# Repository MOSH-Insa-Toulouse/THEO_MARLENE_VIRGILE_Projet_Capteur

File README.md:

# THEO_MARLENE_VIRGILE_Projet_Capteur
Ce projet s'inscrit dans l'UF **"Du capteur au banc de Test"** en 4ème année Génie Physique, à l'INSA de Toulouse. 
***
Ce dernier a pour but l'élaboration d'un **capteur de déformation** à bas coût à base de graphite, dont le fonctionnement est basé sur le principe de déplacement des électrons entre les nanoparticules par effet tunnel. 
La contrainte mécanique appliquée modifiant la distance entre les particules, la conductivité électrique de la couche de graphite subit elle aussi une modification. La déformation du capteur créé grâce à un dépôt au crayon à papier engendre donc une variation de résistance alors mesurable.
*** 
Dans ce dossier sont présentées les différentes étapes que nous avons suivies : du design de notre shield, à notre code Arduino en passant par la réalisation d'une application pour téléphone et d'un banc de mesure réalisé en impression 3D. 

## Sommaire 

* [1. Description du projet et détail des livrables](#PremiereSection) 
* [2. Arduino](#DeuxiemeSection)
  * [2.1. Librairies utilisées](#DeuxiemeSection1)
  * [2.2. Code Arduino](#DeuxiemeSection2)
* [3. KICAD](#TroisiemeSection)  
  * [3.1 Symboles et empreintes](#TroisiemeSection1)
  * [3.2 Schématique](#TroisiemeSection2)
  * [3.3 Placement des composants](#TroisiemeSection3)
  * [3.4 Visualisation 3D](#TroisiemeSection4)
* [4. Fabrication du shield](#QuatriemeSection)
  * [4.1 Réalisation du PCB](#QuatriemeSection1)
  * [4.2 Perçage et soudure](#QuatriemeSection2)
* [5. Application Android](#CinquiemeSection) 
* [6. Tests](#SixiemeSection)
  * [6.1. Banc de test](#SixiemeSection1)
  * [6.2. Résultats obtenus](#SixiemeSection2)
  * [6.3. Analyse des résultats et discussion](#SixiemeSection3)
* [7. Datasheet](#SeptiemeSection)

## 1. Description du projet et détail des livrables

Liste des livrables :

- [x] Un code Arduino permettant une mesure de résistance et un contrôle des fonctionnalités Bluetooth, OLED... 
- [x] Un shield PCB
- [x] Une application android APK 
- [x] Un protocole du banc de test
- [x] Une datasheet des capteurs de déformation

Dans un premier temps, nous avons réalisé un **code Arduino** fonctionnel permettant de contrôler un amplificateur transimpédance, un encodeur rotatoire, un écran OLED ainsi qu'un module Bluetooth. Nous l'avons ensuite testé en effectuant nos premiers branchements.
Ensuite, nous avons réalisé le design de notre **shield** à l'aide du logiciel *KICAD*, nous l'avons fabriqué, puis nous avons assemblé nos composants dessus.   
A la suite de cela, nous avons utilisé le logiciel *MIT App Inventor* afin de développer une **application téléphone APK**, capable de communiquer et recevoir des données à distance à l'aide du module Bluetooth (notamment de récupérer la résistance ressentie par le capteur et de l'afficher sur un graphique).    
Nous avons également designé puis réalisé, un **banc de mesure** en impression 3D, qui, à l'aide d'un servomoteur nous permet de caractériser la réponse en déformation de nos futurs capteurs.   
Finalement, nous sommes passés à la phase de tests et avons créé nos capteurs, en les "coloriant" avec divers types de crayons à papier (HB,B,...). Nous avons ensuite caractérisé ces derniers en récupérant leur résistance en fonction de leur déformation, et avons ainsi pu établir une **datasheet**.

## 2. Arduino

### 2.1. Librairies utilisées

Pour développer notre code, nous avons utilisé plusieurs librairies :["Adafruit_GFX_Library"](/Librairies/Adafruit_GFX_Library) et ["Adafruit_SSD1306"](/Librairies/Adafruit_SSD1306) nous permettant le contrôle de nos modules, ainsi que la librairie [Adafruit_BusIO](/Librairies/Adafruit_BusIO) permettant de gérer la connexion en I2C et SPI.

### 2.2. Code Arduino

Le code [prog_arduino](/Programme%20Arduino/prog_arduino) développé sous Arduino IDE permet d'assurer la communication de tous les éléments de notre carte Arduino (Module Bluetooth, Oled et encodeur rotatoire) afin de réaliser des fonctions voulues. Nous avons ainsi réalisé quatre menus différents qui permettent de réaliser des tâches différentes. 

- Le premier menu permet d'afficher sur l'Oled la valeur de résistance de la jauge de contrainte traduite par l'acquisition de la tension de sortie de notre circuit électronique. Il permet aussi d'envoyer via le module bluetooth la valeur de tension mesurée entre 0 et 5 volts, sous la forme d'un nombre codé en 8 bits : 0 correspondant à 0V et 255 correspondant à 5V. L'objectif de cet envoi est d'ensuite le récupérer via notre application APK pour pouvoir traiter les données.
- Le second menu est assez similaire. La seule différence réside sur l'affichage de l'Oled. On n'affiche plus la valeur de résistance mais la valeur de tension. 
-  Le troisième menu permet de définir un temps d'acquisition sur l'application. On choisit la valeur en secondes grâce à l'encodeur rotatoire et lorsqu'on sélectionne la valeur choisie, elle s'envoie par Bluetooth pour être récupérée et enregistrée par l'application.
-  Le quatrième menu fonctionne de la même manière que le troisième mais permet de changer la valeur de R2 que l'on a laissé variable afin de s'adapter à la plage de mesure de la résistance du capteur. On entre la valeur voulue grâce à l'encodeur rotatoire. 

Les codes contenus dans les dossiers [BT_Test](/Programme%20Arduino/BT_Test), [ENC_TEST](/Programme%20Arduino/ENC_TEST) et [OLED_TEST](/Programme%20Arduino/OLED_TEST) permettent de vérifier individuellement l'état de fonctionnement de chaque module ajouté à notre shield. 

Enfin, Le code Arduino [Servomoteur](/Programme%20Arduino/Banc%20de%20test/Servomoteur) permet de contrôler notre banc de test et sera plus amplement expliqué dans la partie **6. Tests**.

## 3. KICAD

### 3.1. Symboles et empreintes
- Module Bluetooth 

- Encodeur rotatoire 

- Ecran OLED 

- Amplificateur LTC 1050

### 3.2. Schématique de l'ensemble 

Une fois les empreintes créées, nous avons pu réaliser le Eeschema de notre shield. En haut à droite sont représentées les broches de la carte Arduino. Au centre est représenté l'amplificateur transimpédance, et en bas l'écran OLED, le module Bluetooth et l'encodeur rotatoire.

### 3.3. Placement des composants

### 3.4. Visualisation 3D

## 4. Fabrication du shield
### 4.1. Réalisation du PCB

 Nous avons ensuite pu fabriquer le PCB sur une plaquette d'epoxy recouverte d'une fine couche de cuivre (environ 60µm).  
 Tout d'abord, nous avons imprimé notre modélisation du PCB sur du papier calque, puis, une insolation aux UV pendant 2 minutes a permis de transposer cette "silhouette" sur notre couche d'epoxy, permettant ainsi de déposer une résine protectrice, qui grâce à un révélateur, a pu être retirée aux endroits désirés.  
 Ensuite, la plaquette a été déposée dans un bain de perchlorure de fer afin d'être gravée (environ 8 minutes). A la suite de cela, le cuivre non protégé par la résine a alors été retiré, permettant d'obtenir le PCB modélisé en amont.  
 Pour finir, de l'acétone a été appliquée sur la plaquette pour éliminer les dernières traces de résine.

### 4.2. Perçage et soudure

Une fois le PCB réalisé, nous sommes passés au perçage de trous sur notre plaquette à l'aide d'une perçeuse électrique afin d'insérer nos composants : 
- 0.8mm de diamètre pour l'AOP, les résistances et les capacités
- 1mm de diamètre pour les connecteurs de l'Arduino et des headers des différents modules (pinces du capteur, bluetooth, encodeur rotatoire, écran OLED)

Enfin, nous avons soudé chaque composant à l'aide d'un fer à souder.

## 5. Application Android

[L'application](/Application) développée sous MIT App Inventor, un site internet permettant de designer des applications en ligne, permet d'établir la liaison entre les données relevées par l'arduino et le traitement de celles-ci, en direct puis via la création d'un fichier de données. 

Concrètement, l'application a été designée pour corréler avec le code arduino (cf 2.). Elle permet ainsi de se connecter à un module bluetooth chargé d'envoyer la tension relevée, qui sera traduite en résistance pour le capteur. Lorsque l'on est connecté, l'application est capable d'effectuer 3 tâches principales : 
- Relever la tension envoyée par Bluetooth, afficher la valeur de résistance correspondante, de manière numérique et graphique et la traduire dans un fichier texte. Cette fonction est commandée par un système Start/Stop.
- Effectuer une acquisition selon un temps donné. Il faut au préalable définir le temps d'acquisition via l'arduino. Ce temps vient remplacer le Start/Stop, sinon la fonction est la même que précédemment.
- Modifier la valeur de résistance de R2. Pour cela, il faut rentrer la valeur via l'arduino.

## 6. Tests
### 6.1. Banc de test

Pour réaliser nos tests, nous avons utilisé 2 bancs différents ; l'un déjà existant et pensé par nos prédécesseurs et un autre par nos soins lors de la réalisation du projet.

#### Le [banc de test](/Banc%20de%20test) que nous avons imaginé a été modélisé via un logiciel de CAO et ensuite imprimé grâce à une imprimante 3D. 

Il permet de mesurer la déformation du capteur en fonction du temps grâce à une rotation induite par un servomoteur et répond à deux problématiques :
 - La première étant la limite principale du banc de test déjà existant : il était destructif. En effet à chaque utilisation de celui-ci le capteur devenait inutilisable par la suite. Il nous était donc impossible de revenir aux valeurs initiales de résistances après passage du capteur sur le banc de test. 
- La seconde étant la volonté d’observer l’évolution en dynamique de la réponse du capteur afin de déterminer une potentielle fatigue de celui-ci lors d’un test cyclique. 

Nous avons donc réfléchi à un design permettant une installation fixe du capteur qui ne nécessitait plus d’action extérieure au cours de la mesure, et qui pouvait faire périodiquement une application de contrainte identique sur notre capteur. Pour cela, notre banc a été conçu en 3 parties : le socle, la pièce « escargot » et le servomoteur, pilotés via [un code Arduino](/Programme%20Arduino/Banc%20de%20Test/Servomoteur) supplémentaire. 

**Le socle**

Le socle est la pièce massive qui permet de fixer le servomoteur et le capteur afin de ne pas avoir à retoucher le système entre les mesures.  

•	 La languette sur le côté gauche représente la zone permettant de fixer le capteur à l’aide des pinces conductrices.   
•	 Le demi cercle vide au milieu de la pièce correspond à la zone permettant la rotation de la pièce « escargot ».  
•	 L’encoche qui traverse la pièce dans la largeur permet de glisser le servomoteur et de le maintenir dans la position souhaitée.  

**La pièce « escargot »**

Cette pièce est un embout pour le servomoteur : l’extrémité libre du capteur repose dessus lorsqu’il est fixé sur le banc. 
Le rayon de l’embout augmente d’un millimètre tous les dix degrés de rotation ce qui permet d’avoir une variation du rayon entre 5,5 mm et 21,5 mm sur l’ensemble de la rotation du servomoteur.   

Nous souhaitions pouvoir remonter à la déformation en connaissant la longueur du rayon or après plusieurs tentatives, nous nous sommes rendus compte qu’il était difficile de remonter à cette valeur en compression avec la composition géométrique de ce banc de test.   

**Le servomoteur**

Nous avons choisi d’utiliser le servomoteur SG90 car parmi ceux à notre disposition, c’est celui dont les dimensions étaient les plus adaptées pour notre capteur.   
En effet sa petite taille nous permet d’y fixer un embout de plus petite taille qui nous assure de rester dans le domaine de la déformation élastique du papier puisque nous pouvons  appliquer des déformations plus faibles et plus précises.   
Utiliser un servomoteur nous permet de gérer facilement la rotation de la pièce «escargot», et in extenso de fixer facilement la plage de déformation du capteur à l’aide du code Arduino. 

**Le code Arduino**

Nous avons utilisé [ce code Arduino](/Programme%20Arduino/Banc%20de%20test/Servomoteur) qui nous permet de changer la plage de rotation du servomoteur. Il nous permet en modifiant les lignes 17 et 22 de changer la plage de rotation du servomoteur. L’objectif étant de balayer la plus grande différence de rayon possible tout en ne dépassant jamais le bout de course de la pièce escargot afin de ne pas détruire le capteur.  

#### Le banc de test déjà réalisé composé de 7 demi-cercles dont les rayons varient de 1 à 2,5 cm. 

### 6.2. Résultats obtenus

**Avec le banc de test utilisant le servomoteur**

Nous pouvons voir que la jauge réagit de façon périodique à la contrainte du banc en dynamique. 
En effet, lors de la diminution du rayon de la pièce en escargot, nous observons une augmentation quasi-linéaire de la résistance (cf courbe ci-dessus zone 1). 
Lors de l'augmentation de celui-ci, nous observons une diminution quasi-linéaire de la résistance de la jauge de contrainte (cf courbe ci-dessus zone 2).
Nous observons également une plage de données instable entre ces deux phases. Cette réponse du capteur est due à l’imperfection de notre banc (cf courbe ci-dessus zone 3). En effet, lorsque l’on arrive au bout de la course du servomoteur, le capteur ne suit pas complètement l’évolution du rayon de courbure, et entre en contact avec une autre surface de la pièce en « escargot » que celle souhaitée. 

**Avec le banc de test déjà réalisé**

Comme nous pouvons l’observer sur les graphiques ci-dessus, la plupart des réponses des jauges aux déformations appliquées à l’aide du banc de test statique suivent une évolution quasi-linéaire. 

La résistance sans contrainte varie du simple au double entre deux jauges produites par le même type de crayon à papier. 

Les variations de résistance sont plus importantes lorsque la dureté du crayon est plus élevée. En effet, pour le HB nous avons pu observer au maximum une variation de 5 à 20 MOhms et pour le 2B de 4 à 5 MOhms. 

Les facteurs de jauge obtenus en faisant une approximation linéaire sont de :
- 6,5 et 3,2 pour les essais 1 et 2 avec des jauges dessinées avec des crayons 2B
- 6,1 et 11,4 pour les essais 1 et 2 avec des jauges dessinées avec des crayons B
- 13,1 et 27,2 pour les essais 1 et 2 avec des jauges dessinées avec des crayons HB

### 6.3. Analyse des résultats et discussion

Nous observons à l’aide de **notre banc de test** utilisant le servomoteur que le capteur retrouve sa valeur initiale de résistance entre chaque mise sous contrainte. Nous n’observons donc pas de fatigue de la jauge dans la gamme de contraintes que nous appliquons : il faudrait effectuer des tests sur de très longues périodes avant d’apercevoir d’éventuelles fatigues. 

Concernant les imprécisions de la zone de mesure se situant en bout de course du servomoteur, plusieurs améliorations sont envisageables : 
 - Concevoir la pièce « escargot » en miroir, de façon à toujours avoir un rayon plus petit sous la jauge au lieu du contraire actuellement
 - Repenser la pièce afin de pouvoir fixer directement l’extrémité du capteur à la pièce « escargot »

Nous aurions pu également réfléchir en amont au calcul de contrainte qui aurait été plus pertinent qu’un simple relevé de résistance.  
  
Ces différents résultats mettent en valeur les avantages et les limites de ce type de jauges de contrainte.   

Pour ce qui est du **banc de test déjà réalisé**, nous constatons que les jauges réalisées ont, d'après les essais, des facteurs de jauge très élevés avec l’utilisation de crayons à papier à pointe dure, mais que, si le crayon dépose trop peu de graphite, des problèmes de continuité électrique se posent.  

Une des principales limites est donc la dépose du graphite. En effet, nous remarquons des différences de quasiment un facteur 2 entre les facteurs de jauge des capteurs dessinés en 2B, B et HB. 
Ces différences peuvent être dûes à :
 - la non-répétabilité de la mesure et la destruction du capteur en fonction de la manipulation de la jauge et du banc
 - le dépôt de graphite sur le papier : la pression avec le crayon à papier, le nombre de passages du crayon, la précision du tracé    

Il faudrait réfléchir à un procédé permettant un dépôt uniforme, précis et répétable. Une impression mécanique automatisée serait une option pour rendre les facteurs de jauge plus constants.  

Nous pouvons tout de même conclure que la confection de jauges de contrainte en graphite est réalisable et permet de créer des jauges avec de très bon facteurs de jauge. 
Néanmoins, le processus de dessin doit être optimisé car il y a beaucoup trop de paramètres qui ne permettent pas de garantir la qualité de la jauge de contrainte. 

## 7. Datasheet

La [Datasheet](/Datasheet) présente l'ensemble des caractéristiques des jauges que nous avons réalisées ainsi que du shield qui permet de traduire un relevé de tension en mesure de résistance. L'objectif final est de revenir à une mesure de déformation.

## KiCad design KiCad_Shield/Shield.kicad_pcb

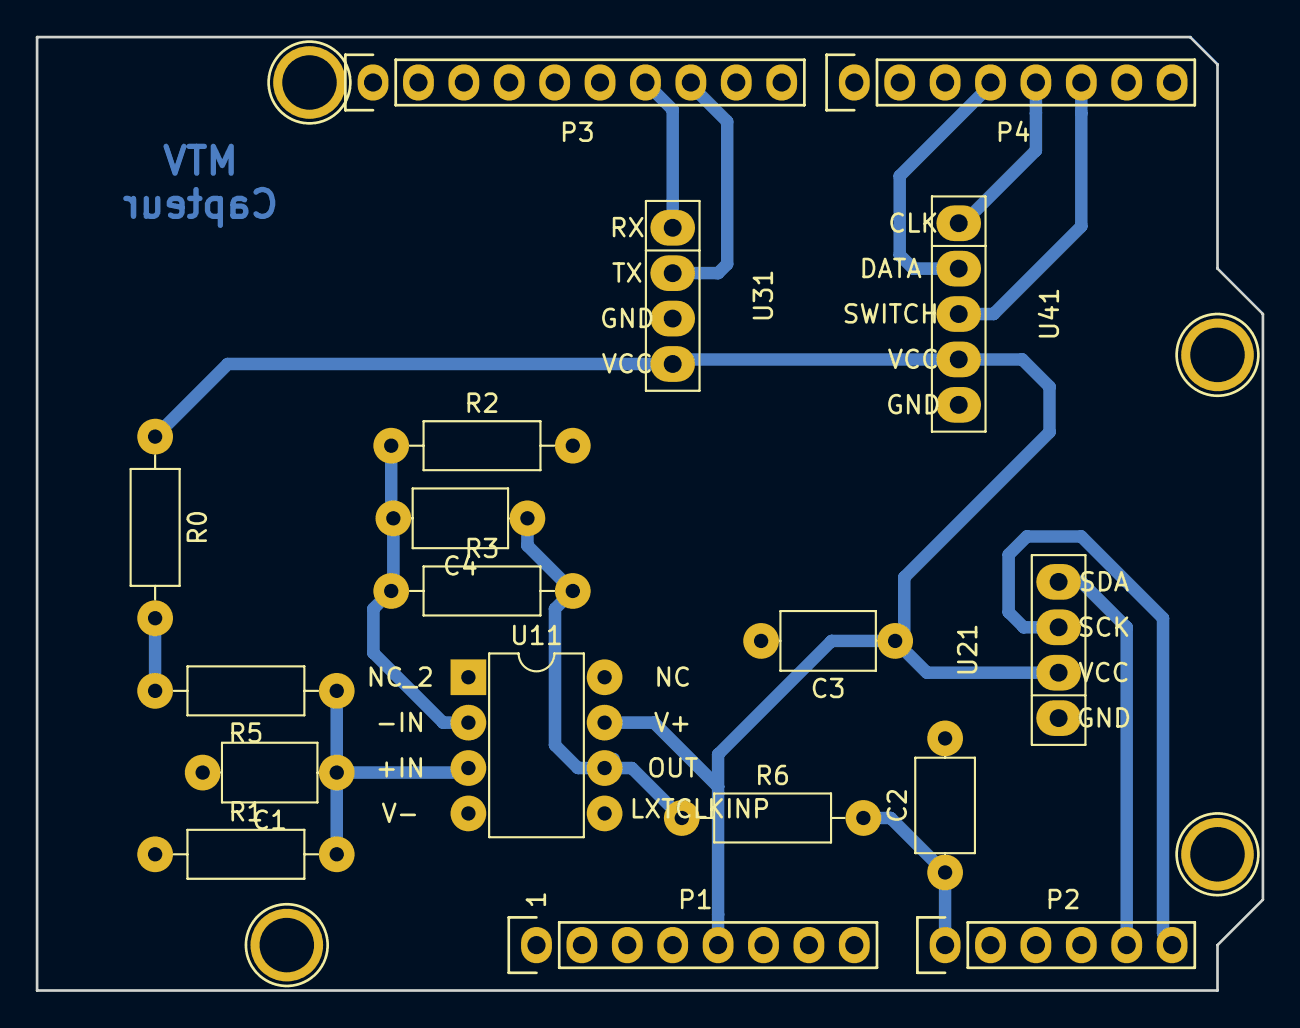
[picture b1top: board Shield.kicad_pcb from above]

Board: 2 copper layers, 68.6 x 53.3 mm, 22 parts (0 on the bottom side), 14 nets.

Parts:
C1, C2, C3: 100n; C_Axial_L5.1mm_D3.1mm_P7.50mm_Horizontal
C4: 1µ; C_Axial_L5.1mm_D3.1mm_P7.50mm_Horizontal
P1: Power; Socket_Strip_Arduino_1x08
P2: Analog; Socket_Strip_Arduino_1x06
P3: Digital; Socket_Strip_Arduino_1x10
P4: Digital; Socket_Strip_Arduino_1x08
P5, P6, P7, P8: CONN_01X01; Arduino_1pin
R0: Rsensor; R_Axial_DIN0207_L6.3mm_D2.5mm_P10.16mm_Horizontal
R1, R3: 100k; R_Axial_DIN0207_L6.3mm_D2.5mm_P10.16mm_Horizontal
R2, R6: 1k; R_Axial_DIN0207_L6.3mm_D2.5mm_P10.16mm_Horizontal
R5: 10k; R_Axial_DIN0207_L6.3mm_D2.5mm_P10.16mm_Horizontal
U11: LTC1050
U21: OLED_0.91
U31: Bluetooth-HC05
U41: ENCODEUR_KY_040; ENCODEUR_KY040

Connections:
+5V: C3.1, P1.5, R0.1, U11.7, U21.2, U31.1, U41.4
ADC: C2.1, P2.1, R6.2
CLK: P4.5, U41.1
DATA: P4.4, U41.2
GND: C1.2, C2.2, C3.2, P1.6, P1.7, P3.4, R1.1, R2.2, U11.4, U21.1, U31.2, U41.5
IN+: C1.1, R1.2, R5.1, U11.3
IN-: C4.2, R2.1, R3.1, U11.2
unnamed: C4.1, R3.2, R6.1, U11.6
unnamed: R0.2, R5.2
RX: P3.8, U31.3
SCK: P2.6, P3.1, U21.3
SDA: P2.5, P3.2, U21.4
SWITCH: P4.6, U41.3
TX: P3.7, U31.4

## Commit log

2021-03-10 Programme arduino
2021-03-10 arduino
2021-03-10 KiCad ajout
2021-03-12 Tests Arduino
2021-03-15 Test Encoder OK
2021-03-15 Programme Arduino OK
2021-03-16 banc de test 3D
2021-03-16 simplification arduino
2021-03-17 pin rx tx changés Arduino
2021-03-17 new changes
2021-03-18 piece servo moteur 3D et autres
2021-03-19 ajustement arduino
2021-04-13 ,d,d
2021-04-14 arduino changes
2021-04-14 MAJ README
2021-04-15 Resultats ajoutés
2021-04-15 travail à réaliser
2021-04-22 Explications application
2021-04-26 README.md
2021-04-26 Librairies
2021-04-26 A faire
2021-04-27 modification Arduino et readme
2021-04-27 Suppression de répertoires
2021-04-27 ImagesShield
2021-04-27 Images_Shield
2021-04-27 Images
2021-04-28 Résultats
2021-04-29 image servo moteur
2021-05-02 Readme et autres
2021-05-02 datasheet et readme
2021-05-02 readme
2021-05-02 fautes readme
2021-05-05 erreurs datasheet
2021-05-05 Erreur datasheet
